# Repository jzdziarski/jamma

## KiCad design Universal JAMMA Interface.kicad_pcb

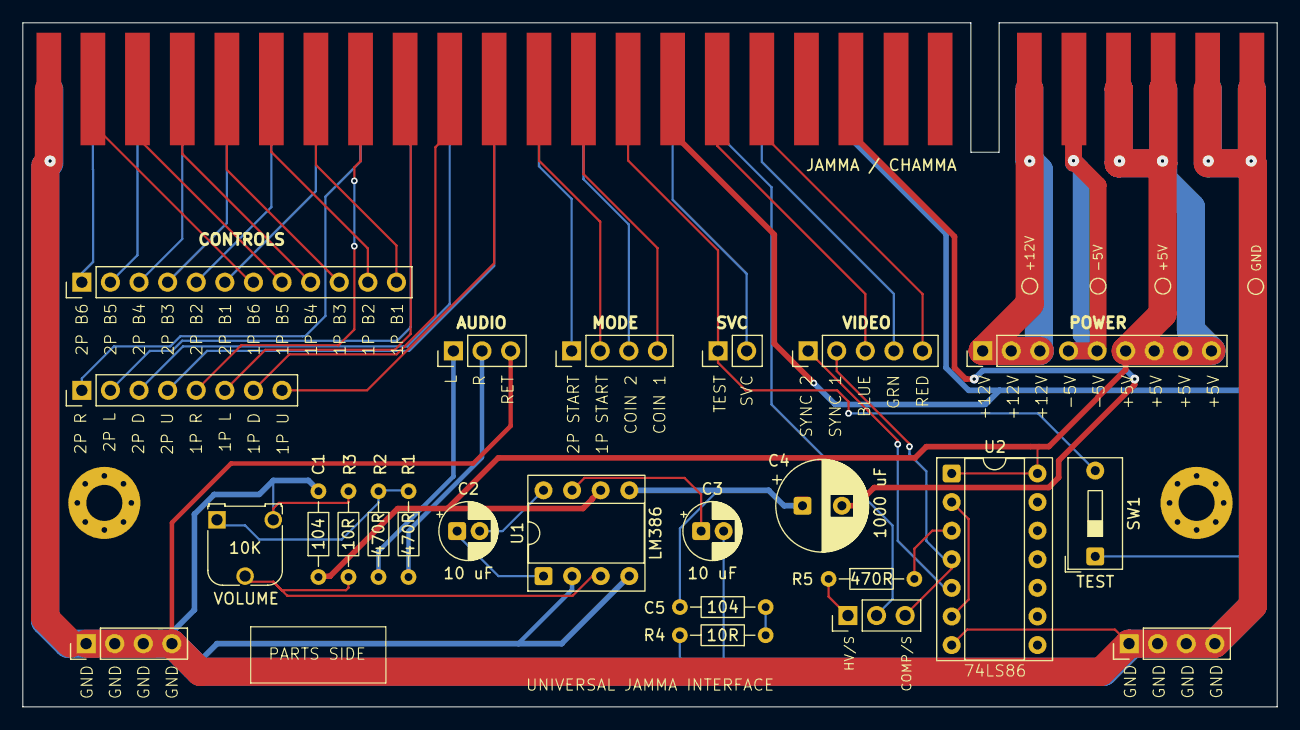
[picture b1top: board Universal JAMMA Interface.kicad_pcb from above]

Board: 2 copper layers, 111.4 x 60.8 mm, 29 parts (0 on the bottom side), 49 nets.

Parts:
+5V, +12V: TestPoint_Pad_D1.0mm
-5V: TestPoint_Pad_D1.0mm
AUDIO: PinHeader_1x03_P2.54mm_Vertical
C1, C5: 104; R_Axial_DIN0204_L3.6mm_D1.6mm_P7.62mm_Horizontal
C2, C3: 10 uF; CP_Radial_D5.0mm_P2.00mm
C4: 1000 uF; CP_Radial_D8.0mm_P3.50mm
CONTROLS: PinHeader_1x12_P2.54mm_Vertical
DIRECTIONALS: PinHeader_1x08_P2.54mm_Vertical
GND: TestPoint_Pad_D1.0mm
Ground: PinHeader_1x04_P2.54mm_Vertical
Ground#2: PinHeader_1x04_P2.54mm_Vertical
HV/S: PinHeader_1x03_P2.54mm_Vertical
JAMMA / CHAMMA: HDR_JAMMA_56P_EDGE_CONNECTOR
MODE: PinHeader_1x04_P2.54mm_Vertical
POWER: PinHeader_1x09_P2.54mm_Vertical
R1, R2, R5: 470R; R_Axial_DIN0204_L3.6mm_D1.6mm_P7.62mm_Horizontal
R3, R4: 10R; R_Axial_DIN0204_L3.6mm_D1.6mm_P7.62mm_Horizontal
SVC: PinHeader_1x02_P2.54mm_Vertical
TEST: SW1; SW_DIP_SPSTx01_Slide_9.78x4.72mm_W7.62mm_P2.54mm
U1: LM386; DIP-8_W7.62mm_Socket
U2: DIP-14_W7.62mm_Socket
VIDEO: PinHeader_1x05_P2.54mm_Vertical
VOLUME: 10K; Potentiometer_Runtron_RM-065_Vertical

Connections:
1P_B1: CONTROLS.12, JAMMA / CHAMMA.22
1P_B2: CONTROLS.11, JAMMA / CHAMMA.23
1P_B3: CONTROLS.10, JAMMA / CHAMMA.24
1P_B4: CONTROLS.9, JAMMA / CHAMMA.25
1P_B5: CONTROLS.8, JAMMA / CHAMMA.26
1P_B6: CONTROLS.7, JAMMA / CHAMMA.27
1P_D: DIRECTIONALS.7, JAMMA / CHAMMA.19
1P_L: DIRECTIONALS.6, JAMMA / CHAMMA.20
1P_R: DIRECTIONALS.5, JAMMA / CHAMMA.21
1P_START: JAMMA / CHAMMA.17, MODE.2
1P_U: DIRECTIONALS.8, JAMMA / CHAMMA.18
2P_B1: CONTROLS.6, JAMMA / CHAMMA.Z
2P_B2: CONTROLS.5, JAMMA / CHAMMA.a
2P_B3: CONTROLS.4, JAMMA / CHAMMA.b
2P_B4: CONTROLS.3, JAMMA / CHAMMA.c
2P_B5: CONTROLS.2, JAMMA / CHAMMA.d
2P_B6: CONTROLS.1, JAMMA / CHAMMA.e
2P_D: DIRECTIONALS.3, JAMMA / CHAMMA.W
2P_L: DIRECTIONALS.2, JAMMA / CHAMMA.X
2P_R: DIRECTIONALS.1, JAMMA / CHAMMA.Y
2P_START: JAMMA / CHAMMA.U, MODE.1
2P_U: DIRECTIONALS.4, JAMMA / CHAMMA.V
+5V: +5V.1, C1.1, JAMMA / CHAMMA.3, JAMMA / CHAMMA.4, JAMMA / CHAMMA.C, JAMMA / CHAMMA.D, POWER.6, POWER.7, POWER.8, POWER.9, U1.6, U2.1, U2.14
+12V: +12V.1, JAMMA / CHAMMA.6, JAMMA / CHAMMA.F, POWER.1, POWER.2, POWER.3
-5V: -5V.1, JAMMA / CHAMMA.5, JAMMA / CHAMMA.E, POWER.4, POWER.5
AUDIO_L: AUDIO.1, R2.2
AUDIO_MONO: R1.1, R2.1, VOLUME.1
AUDIO_R: AUDIO.2, R1.2
C5_R4: C5.1, R4.1
COIN_1: JAMMA / CHAMMA.16, MODE.4
COIN_2: JAMMA / CHAMMA.T, MODE.3
GND: AUDIO.3, C1.2, C3.2, GND.1, Ground.1, Ground.2, Ground.3, Ground.4, Ground#2.1, Ground#2.2, Ground#2.3, Ground#2.4, JAMMA / CHAMMA.1, JAMMA / CHAMMA.2, JAMMA / CHAMMA.14, JAMMA / CHAMMA.28, JAMMA / CHAMMA.A, JAMMA / CHAMMA.B, JAMMA / CHAMMA.L, JAMMA / CHAMMA.f, R3.2, R4.2, TEST.1, U1.2, U1.4, U2.7, VOLUME.3
PREAMP: R3.1, U1.3, VOLUME.2
PREAMP_OUT: C4.1, C5.2, U1.5
SERVICE: JAMMA / CHAMMA.R, SVC.2
SPKR+: C4.2, JAMMA / CHAMMA.10
TEST: JAMMA / CHAMMA.15, SVC.1, TEST.2
U4_BYPASS: C3.1, U1.7
U4_GAIN_P1: C2.1, U1.1
U4_GAIN_P8: C2.2, U1.8
VID_B: JAMMA / CHAMMA.13, VIDEO.3
VID_CSYNC: HV/S.2, JAMMA / CHAMMA.P
VID_G: JAMMA / CHAMMA.N, VIDEO.4
VID_NXOR: HV/S.1, R5.1
VID_NXOR_R5: R5.2, U2.3
VID_R: JAMMA / CHAMMA.12, VIDEO.5
VID_SYN1: HV/S.3, U2.4, VIDEO.2
VID_SYN2: U2.5, VIDEO.1
VID_XOR: U2.2, U2.6

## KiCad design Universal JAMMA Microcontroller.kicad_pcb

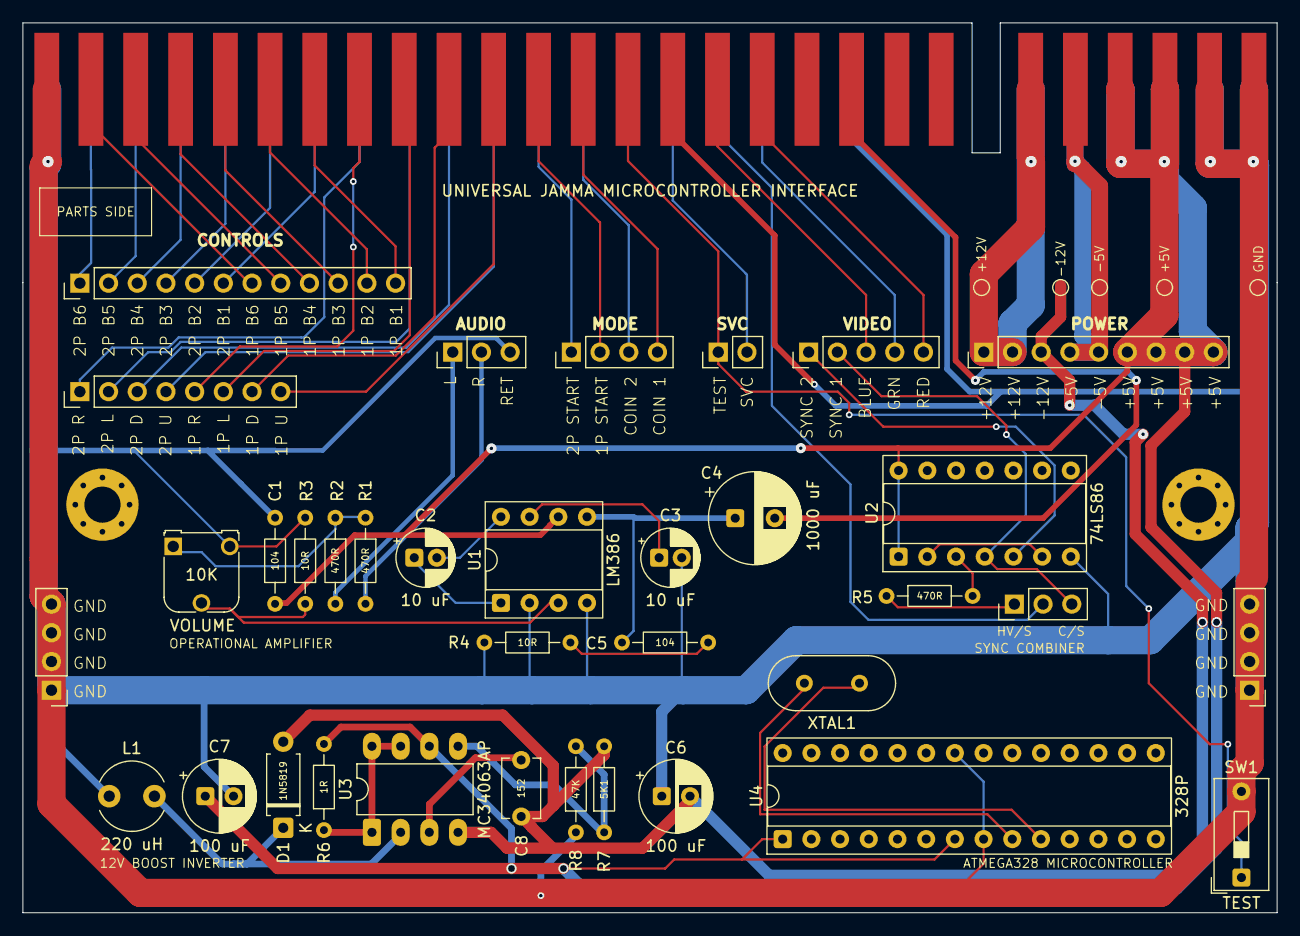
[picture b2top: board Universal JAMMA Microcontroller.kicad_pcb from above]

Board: 2 copper layers, 111.0 x 78.8 mm, 41 parts (0 on the bottom side), 56 nets.

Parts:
+5V, +12V: TestPoint_Pad_D1.0mm
-5V, -12V: TestPoint_Pad_D1.0mm
AUDIO: PinHeader_1x03_P2.54mm_Vertical
C1, C5: 104; R_Axial_DIN0204_L3.6mm_D1.6mm_P7.62mm_Horizontal
C2, C3: 10 uF; CP_Radial_D5.0mm_P2.00mm
C4: 1000 uF; CP_Radial_D8.0mm_P3.50mm
C6, C7: 100 uF; CP_Radial_D6.3mm_P2.50mm
C8: 152; C_Disc_D5.1mm_W3.2mm_P5.00mm
CONTROLS: PinHeader_1x12_P2.54mm_Vertical
D1: 1N5819; D_A-405_P7.62mm_Horizontal
DIRECTIONALS: PinHeader_1x08_P2.54mm_Vertical
GND: TestPoint_Pad_D1.0mm
Ground: PinHeader_1x04_P2.54mm_Vertical
Ground#2: PinHeader_1x04_P2.54mm_Vertical
HV/S: PinHeader_1x03_P2.54mm_Vertical
JAMMA: HDR_JAMMA_56P_EDGE_CONNECTOR
L1: 220 uH; L_Radial_D6.0mm_P4.00mm
MODE: PinHeader_1x04_P2.54mm_Vertical
POWER: PinHeader_1x09_P2.54mm_Vertical
R1, R2, R5: 470R; R_Axial_DIN0204_L3.6mm_D1.6mm_P7.62mm_Horizontal
R3, R4: 10R; R_Axial_DIN0204_L3.6mm_D1.6mm_P7.62mm_Horizontal
R6: 1R; R_Axial_DIN0204_L3.6mm_D1.6mm_P7.62mm_Horizontal
R7: 5K1; R_Axial_DIN0204_L3.6mm_D1.6mm_P7.62mm_Horizontal
R8: 47K; R_Axial_DIN0204_L3.6mm_D1.6mm_P7.62mm_Horizontal
SVC: PinHeader_1x02_P2.54mm_Vertical
TEST: SW1; SW_DIP_SPSTx01_Slide_9.78x4.72mm_W7.62mm_P2.54mm
U1: LM386; DIP-8_W7.62mm_Socket
U2: 74LS86; DIP-14_W7.62mm_Socket
U3: MC34063AP; DIP-8_W7.62mm_LongPads
U4: 328P; DIP-28_W7.62mm_Socket
VIDEO: PinHeader_1x05_P2.54mm_Vertical
VOLUME: 10K; Potentiometer_Runtron_RM-065_Vertical
XTAL1: Crystal_HC49-4H_Vertical

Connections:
1P_B1: CONTROLS.12, JAMMA.22
1P_B2: CONTROLS.11, JAMMA.23
1P_B3: CONTROLS.10, JAMMA.24
1P_B4: CONTROLS.9, JAMMA.25
1P_B5: CONTROLS.8, JAMMA.26
1P_B6: CONTROLS.7, JAMMA.27
1P_D: DIRECTIONALS.7, JAMMA.19
1P_L: DIRECTIONALS.6, JAMMA.20
1P_R: DIRECTIONALS.5, JAMMA.21
1P_START: JAMMA.17, MODE.2
1P_U: DIRECTIONALS.8, JAMMA.18
2P_B1: CONTROLS.6, JAMMA.Z
2P_B2: CONTROLS.5, JAMMA.a
2P_B3: CONTROLS.4, JAMMA.b
2P_B4: CONTROLS.3, JAMMA.c
2P_B5: CONTROLS.2, JAMMA.d
2P_B6: CONTROLS.1, JAMMA.e
2P_D: DIRECTIONALS.3, JAMMA.W
2P_L: DIRECTIONALS.2, JAMMA.X
2P_R: DIRECTIONALS.1, JAMMA.Y
2P_START: JAMMA.U, MODE.1
2P_U: DIRECTIONALS.4, JAMMA.V
+5V: +5V.1, C1.1, C7.1, JAMMA.3, JAMMA.4, JAMMA.C, JAMMA.D, POWER.6, POWER.7, POWER.8, POWER.9, R6.2, U1.6, U2.1, U2.14, U3.6, U4.1, U4.7
+12V: +12V.1, JAMMA.6, JAMMA.F, POWER.1, POWER.2
-5V: -5V.1, JAMMA.5, JAMMA.E, POWER.4, POWER.5
-12V: -12V.1, C6.2, C8.1, D1.2, POWER.3, R7.2, U3.4
AUDIO_L: AUDIO.1, R2.2
AUDIO_MONO: R1.1, R2.1, VOLUME.1
AUDIO_R: AUDIO.2, R1.2
C5_R4: C5.1, R4.1
CINV_R7_R8: R7.1, R8.2, U3.5
COIN_1: JAMMA.16, MODE.4
COIN_2: JAMMA.T, MODE.3
GND: AUDIO.3, C1.2, C3.2, C6.1, C7.2, GND.1, Ground.1, Ground.2, Ground.3, Ground.4, Ground#2.1, Ground#2.2, Ground#2.3, Ground#2.4, JAMMA.1, JAMMA.2, JAMMA.14, JAMMA.28, JAMMA.A, JAMMA.B, JAMMA.L, JAMMA.f, L1.1, R3.2, R4.2, R8.1, TEST.2, U1.2, U1.4, U2.7, U4.8, U4.22, VOLUME.3
PB6: U4.9, XTAL1.2
PB7: U4.10, XTAL1.1
PREAMP: R3.1, U1.3, VOLUME.2
PREAMP_OUT: C4.1, C5.2, U1.5
R6: R6.1, U3.1, U3.7, U3.8
SERVICE: JAMMA.R, SVC.2
SPKR+: C4.2, JAMMA.10
SWE: D1.1, L1.2, U3.2
TEST: JAMMA.15, SVC.1, TEST.1
U3_CAP: C8.2, U3.3
U4_BYPASS: C3.1, U1.7
U4_GAIN_P1: C2.1, U1.1
U4_GAIN_P8: C2.2, U1.8
VID_B: JAMMA.13, VIDEO.3
VID_CSYNC: HV/S.2, JAMMA.P
VID_G: JAMMA.N, VIDEO.4
VID_NXOR: HV/S.1, R5.1
VID_NXOR_R5: R5.2, U2.3
VID_R: JAMMA.12, VIDEO.5
VID_SYN1: HV/S.3, U2.4, VIDEO.2
VID_SYN2: U2.5, VIDEO.1
VID_XOR: U2.2, U2.6

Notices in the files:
Universal JAMMA Interface.kicad_pcb:
PCB Design Copyright © 2025, Jonathan Zdziarski
All Rights Reserved
